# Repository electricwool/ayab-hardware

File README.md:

A minimal  ESP32-AYAB shield design containing all essential parts. designed to fit in the tiniest possible board size, costs less than a S3-devkit-C with PCBA and is about 5x5cm, solving the problem of the esp32-AYAB only fits in the KH910. The soldering of a module is very expensive, more expensive than this board. further, the arrangement of the devices in this board have a linear in-out flow so any arbitrary wire-board connectors or modules should work with a simple pin re-mapping. upon reflection this will also work with the raspberry pi GPIO and Arduino if you remove the inline voltage dividers and rearrange the output pins. This is a universal ayab board, simply add microcontroller of your choice.

As the purpose of migrating to ESP32 has been to permit networked features it seems necessary to move beyond the stock s3 and use the octal flash and psram models needed to serve an application. These pin conflicts render all of the removed parts unusable due to lack of IO. knitting machines come with a 12v and 5v rail already so the power supply is also superfluous. In order to enable development only the core features of the esp32 board are preserved. connectors are to be joined to the board via modular cablemaking or sub boards. This means that future revisions and prototying of the board do not incur repeated costs of items like a buzzer and interfacing circuitry but only plugs and a roll of wire.

further investigation reveals that the original sensor boards are capable of operating down to VCC= 3.0V. with 3.3V supply the hall sensors and rotary encoder operates effectively. This greatly reduces the complexity and cost of the board. the comparators and external ADC can be eliminated by using the coprocessor: ULP(esp32) or PIO(rp2350/2040) greatly reducing cost. These are not supported in the arduino framework as they use an extremely old version of the development environment and would require a complete rewrite. the rp2350 has enough IO to support eliminating the GPIO expander. this reduces complexity and size. rp2350 A4 natively supports 3.3V ADC while the esp32 is generally considered to have no ADC due to defective ADC hardware making rp2350 the ideal candidate.

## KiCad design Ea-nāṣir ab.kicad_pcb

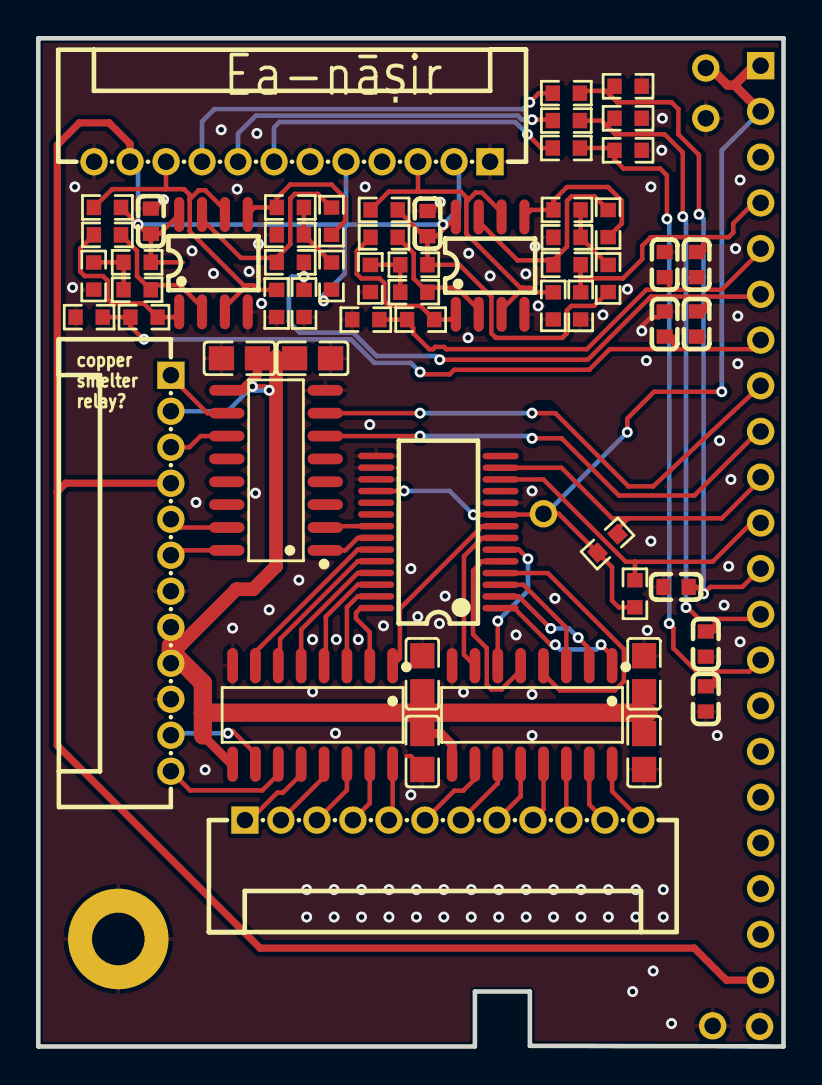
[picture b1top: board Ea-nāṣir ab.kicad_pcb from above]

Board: 2 copper layers, 41.4 x 56.0 mm, 60 parts (0 on the bottom side), 64 nets.

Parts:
1, 3, 4, 5, 6, 7, 8, 9, 10, 11, 12, 13, 14, 15, 16, 17, 18, 19, 20, 21, 22, 23, 24, 25, 26, 27, 28, 29, 30, 40, 41, 42, 43: R0603
C1aaa, C1aaa1, C1aaa2JS20T-S12PHW-00, C1aaac, C1aaad, C1aaax, C1aaay, C1aaaz, C1bbb: C0603
MCP23017: SSOP-28_L10.2-W5.3-P0.65-LS7.8-BL
R1dfghdf: R0603
U4: SOIC-16_L9.9-W3.9-P1.27-LS6.0-BL
cc1, cc2, cc3, cc4, cc5, cc6: C0805
ghfg: R0603
j1, j2, j3: CONN-TH_12P-P2.00_ZX-PH2.0-WZ12P
jhmk: R0603
u2, u3: SOIC-8_L5.0-W4.0-P1.27-LS6.0-BL
ul1: SOIC-16_L9.9-W3.9-P1.27-LS6.0-BL
un2: SOIC-16_L9.9-W3.9-P1.27-LS6.0-BL

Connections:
$1N476: 4.2, 8.2, 17.1
$1N1029: 21.2, 24.1, 26.2
$1N4761: 3.2, 7.2, 16.1
$1N10291: 20.2, 23.1, 25.2
+3V3: 1.1, 22.1, MCP23017.9, MCP23017.18
+5V: 7.1, 8.1, 12.1, 13.1, 25.1, 26.1, C1aaa.1, C1bbb.1, j1.4, j2.2, j2.5, j2.11, u2.8, u3.8
+12V: U4.9, cc1.1, cc2.2, cc3.2, cc4.1, cc5.1, cc6.1, j1.2, j1.8, j1.9, ul1.9, un2.9
/AUX-CONNECTORS/AYAB_SCL: 1.2, MCP23017.12
/AUX-CONNECTORS/AYAB_SDA: 22.2, MCP23017.13
/BROTHER-CONNECTORS/ENC_BELTPHASE: R1dfghdf.1, j2.9
/BROTHER-CONNECTORS/ENC_V1: 5.1, j2.8
/BROTHER-CONNECTORS/ENC_V2: 6.1, j2.7
/BROTHER-CONNECTORS/EOL_L: 10.2, 12.2, j2.10, u2.3, u2.6
/BROTHER-CONNECTORS/EOL_L_N: 27.1, ghfg.2, u2.1
/BROTHER-CONNECTORS/EOL_L_S: 18.1, 29.1, u2.7
/BROTHER-CONNECTORS/EOL_R: 11.2, 13.2, j2.3, u3.3, u3.6
/BROTHER-CONNECTORS/EOL_R_N: 28.1, jhmk.2, u3.1
/BROTHER-CONNECTORS/EOL_R_S: 19.1, 30.1, u3.7
/BROTHER-CONNECTORS/SOL_0: U4.16, j3.5
/BROTHER-CONNECTORS/SOL_1: j3.6, ul1.10
/BROTHER-CONNECTORS/SOL_2: j3.7, ul1.11
/BROTHER-CONNECTORS/SOL_3: j3.8, ul1.12
/BROTHER-CONNECTORS/SOL_4: j3.9, ul1.13
/BROTHER-CONNECTORS/SOL_5: j3.10, ul1.14
/BROTHER-CONNECTORS/SOL_6: j3.11, ul1.15
/BROTHER-CONNECTORS/SOL_7: j3.12, ul1.16
/BROTHER-CONNECTORS/SOL_8: j1.5, un2.15
/BROTHER-CONNECTORS/SOL_9: j1.6, un2.16
/BROTHER-CONNECTORS/SOL_A: U4.10, j1.11
/BROTHER-CONNECTORS/SOL_B: U4.11, j1.12
/BROTHER-CONNECTORS/SOL_C: U4.12, j3.1
/BROTHER-CONNECTORS/SOL_D: U4.13, j3.2
/BROTHER-CONNECTORS/SOL_E: U4.14, j3.3
/BROTHER-CONNECTORS/SOL_F: U4.15, j3.4
/ESP32/ENC_A: 5.2, 14.1, C1aaax.1
/ESP32/ENC_B: 6.2, 15.1, C1aaay.1
/ESP32/ENC_BP: 9.1, C1aaaz.1, R1dfghdf.2
/ESP32/EOL_L_N: 29.2, 40.1, C1aaad.1
/ESP32/EOL_L_P: 27.2, 42.1, C1aaac.1
/ESP32/EOL_R_N: 30.2, 41.1, C1aaa2JS20T-S12PHW-00.1
/ESP32/EOL_R_P: 28.2, 43.1, C1aaa1.1
/SOLENOID DRIVERS/MCU_SOL_0: MCP23017.8, U4.1
/SOLENOID DRIVERS/MCU_SOL_1: MCP23017.7, ul1.7
/SOLENOID DRIVERS/MCU_SOL_2: MCP23017.6, ul1.6
/SOLENOID DRIVERS/MCU_SOL_3: MCP23017.5, ul1.5
/SOLENOID DRIVERS/MCU_SOL_4: MCP23017.4, ul1.4
/SOLENOID DRIVERS/MCU_SOL_5: MCP23017.3, ul1.3
/SOLENOID DRIVERS/MCU_SOL_6: MCP23017.2, ul1.2
/SOLENOID DRIVERS/MCU_SOL_7: MCP23017.1, ul1.1
/SOLENOID DRIVERS/MCU_SOL_8: MCP23017.21, un2.2
/SOLENOID DRIVERS/MCU_SOL_9: MCP23017.22, un2.1
/SOLENOID DRIVERS/MCU_SOL_A: MCP23017.23, U4.7
/SOLENOID DRIVERS/MCU_SOL_B: MCP23017.24, U4.6
/SOLENOID DRIVERS/MCU_SOL_C: MCP23017.25, U4.5
/SOLENOID DRIVERS/MCU_SOL_D: MCP23017.26, U4.4
/SOLENOID DRIVERS/MCU_SOL_E: MCP23017.27, U4.3
/SOLENOID DRIVERS/MCU_SOL_F: MCP23017.28, U4.2
BUZZER12V: j1.3, un2.11
GND: 9.2, 10.1, 11.1, 14.2, 15.2, 16.2, 17.2, 23.2, 24.2, 40.2, 41.2, 42.2, 43.2, C1aaa.2, C1aaa1.2, C1aaa2JS20T-S12PHW-00.2, C1aaac.2, C1aaad.2, C1aaax.2, C1aaay.2, C1aaaz.2, C1bbb.2, MCP23017.10, MCP23017.15, MCP23017.16, MCP23017.17, U4.8, cc1.2, cc2.1, cc3.1, cc4.2, cc5.2, cc6.2, j1.7, j1.10, j2.1, j2.6, j2.12, u2.4, u3.4, ul1.8, un2.8
NET-(U703A1--): 3.1, ghfg.1, u2.2
NET-(U703A--): 4.1, jhmk.1, u3.2
NET-(U703B1-+): 18.2, 20.1, u2.5
NET-(U703B-+): 19.2, 21.1, u3.5
SPARE12V: j1.1, un2.10

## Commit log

2025-11-29 Add files via upload
    a tiny esp32 Ayab shield.
2025-11-30 Create placeholder
2025-12-21 Document sensor voltage readings and interface issues
    Added detailed voltage readings and notes for K carriage and Lace carriage sensors, including issues with the interface circuit and board design.
2025-12-21 Add new hardware information to README
2025-12-21 add project files
2025-12-21 Revise readme for version 2 of interface board
    Updated the readme to reflect changes in version 2 of the interface board, including hardware specifications and sensor configurations.
2025-12-23 update schematic to use ads1015
2025-12-23 Change ADS1115 to ADS1015 in readme
    Updated the readme to reflect the switch from ADS1115 to ADS1015 for improved sensor configuration and reduced MCU pin usage, while noting the trade-off in read time.
2025-12-23 Revise readme for ADS1015 implementation details
    Updated readme to reflect changes in sensor configuration and performance metrics with ADS1015.
